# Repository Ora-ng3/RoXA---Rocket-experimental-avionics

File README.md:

RoXA stands for Rocket experimental avionics. It's my first flight computer (that is more than an arduino with a barometer soldered : ), you can see in [this instructables](https://www.instructables.com/Rocket-Flight-Computer/) a more detailed description of the design and build.

In this repo you'll find the PCB design and manufacturing files, as well as the code. For now it can reliably trigger first and second events. I'm working actively on this project to add reliable data logging and telemetry (and many other things...).

Keywords : Flight computer avionics Rocket Reaction wheel Rogallo

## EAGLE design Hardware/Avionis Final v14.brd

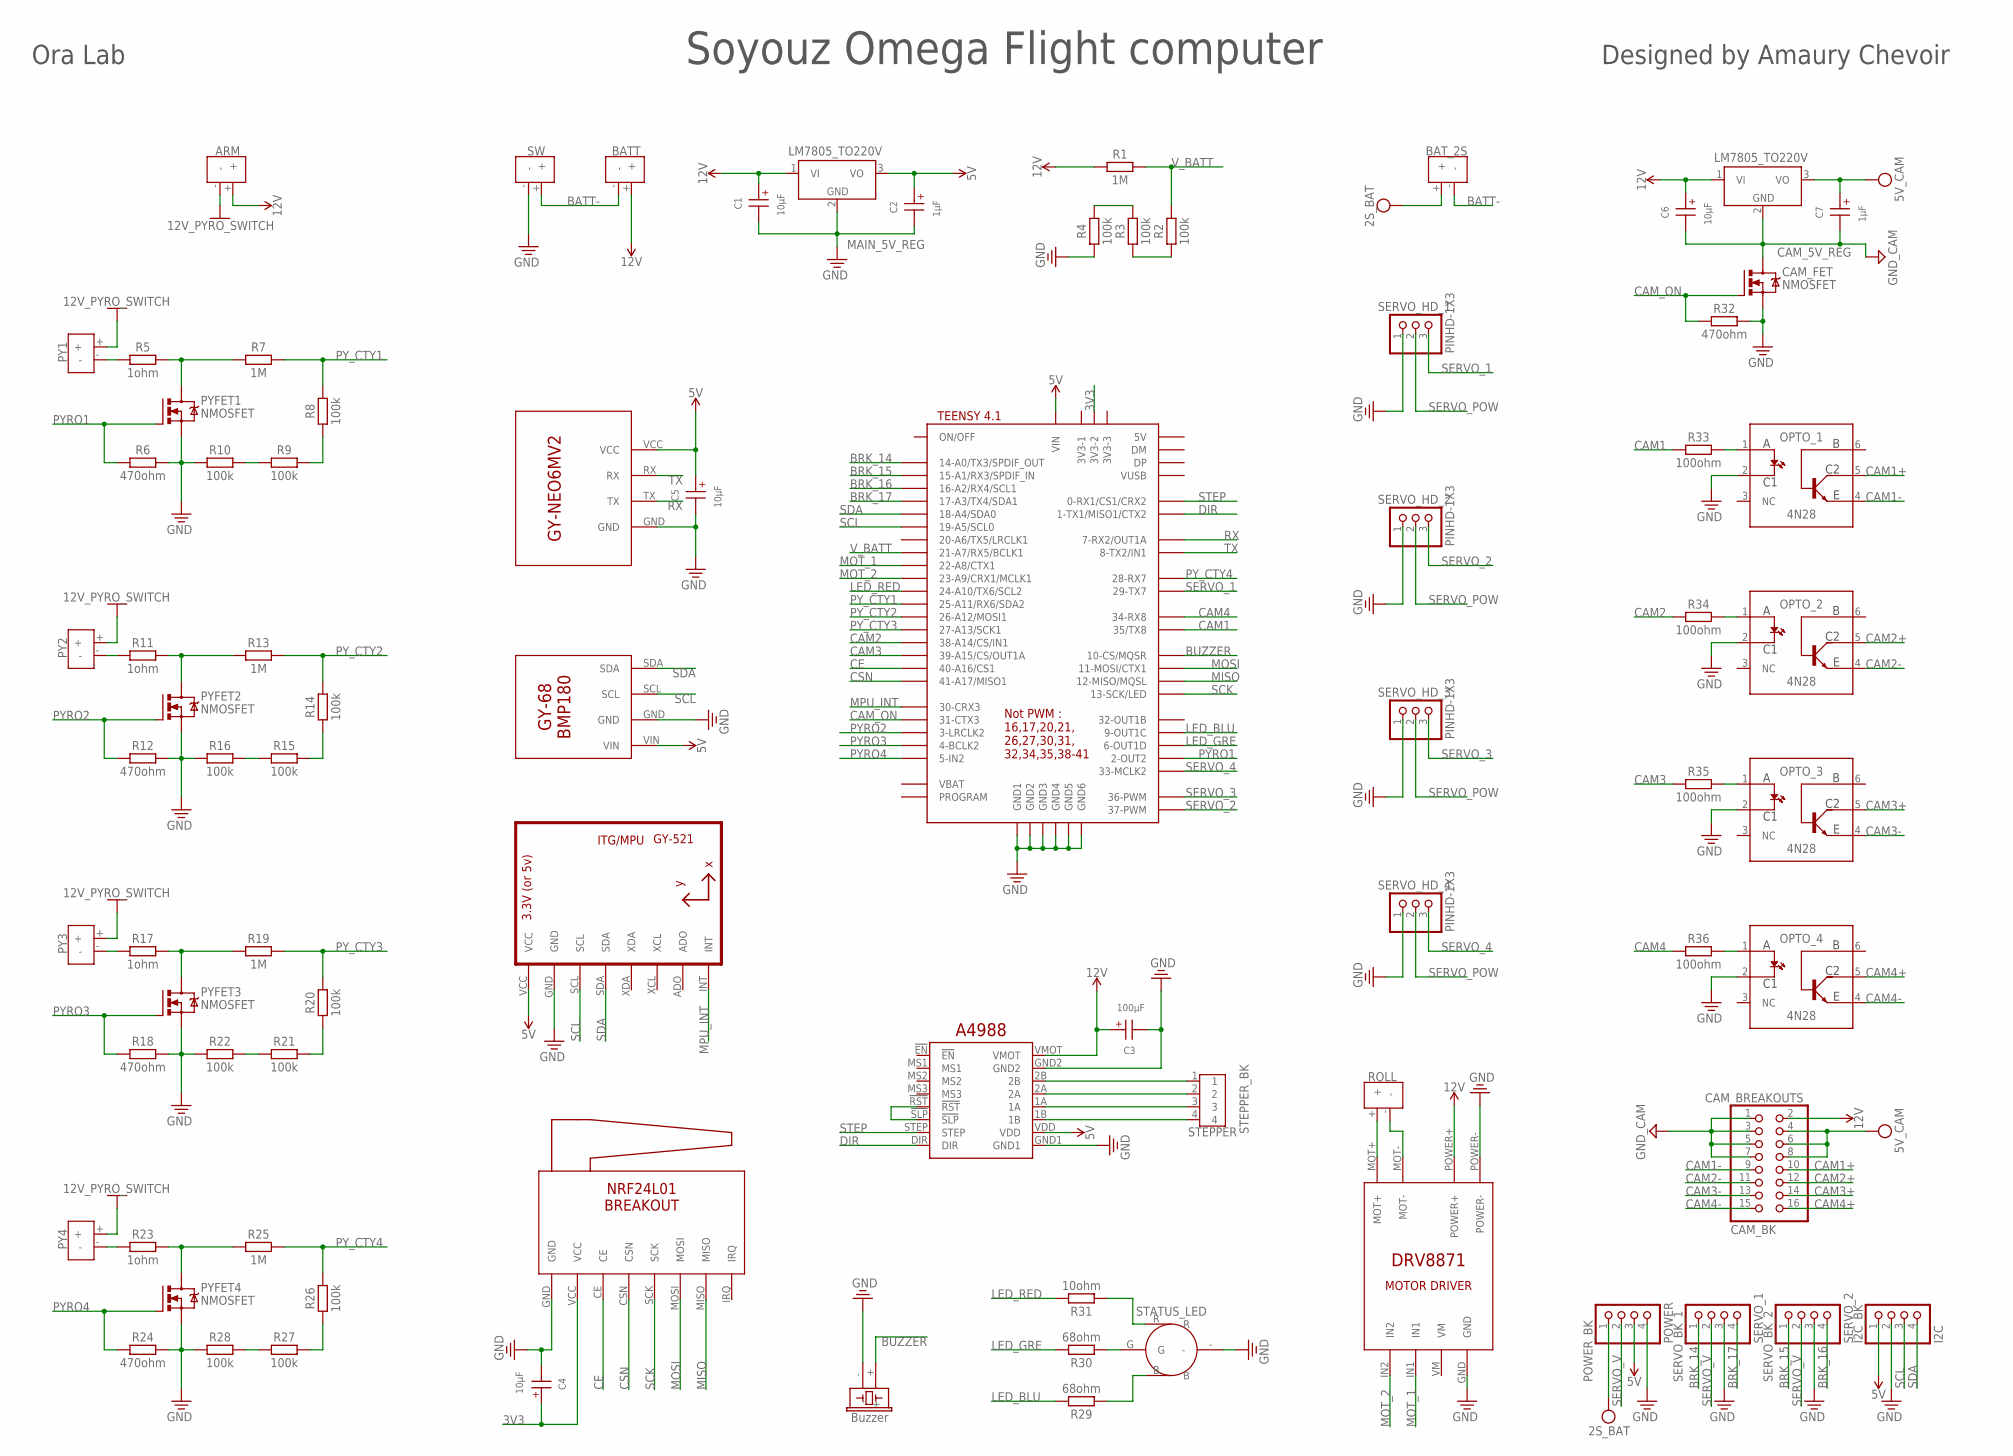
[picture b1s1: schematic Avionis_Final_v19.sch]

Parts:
ARM: TERMBLK_2; TERMBLK_2_LOW
BATT: TERMBLK_2; TERMBLK_2_LOW
BAT_2S: TERMBLK_2; TERMBLK_2_LOW
C1, C4, C5, C6: 10µF; WCAP-AT1H_5X11(DXL)
C2, C7: 1µF; WCAP-AT1H_5X11(DXL)
C3: 100µF; WCAP-AT1H_5X11(DXL)
CAM_5V_REG: LM7805_TO220V; TO220V
CAM_BREAKOUTS: CAM_BK; 2X08
CAM_FET: NMOSFET; TO220BV
I2C_BK: I2C; 1X04
MAIN_5V_REG: LM7805_TO220V; TO220V
OPTO_1, OPTO_2, OPTO_3, OPTO_4: 4N28; DIP762W60P254L712H480Q6B
POWER_BK: POWER; 1X04
PY1, PY2, PY3, PY4: TERMBLK_2; TERMBLK_2_LOW
PYFET1, PYFET2, PYFET3, PYFET4: NMOSFET; TO220BV
R1, R7, R13, R19, R25: 1M; RESAD724W46L381D178B
R2, R3, R4, R8, R9, R10, R14, R15, R16, R20, R21, R22, R26, R27, R28: 100k; RESAD724W46L381D178B
R5, R11, R17, R23: 1ohm; RESAD724W46L381D178B
R6, R12, R18, R24, R32: 470ohm; RESAD724W46L381D178B
R29, R30: 68ohm; RESAD724W46L381D178B
R31: 10ohm; RESAD724W46L381D178B
R33, R34, R35, R36: 100ohm; RESAD724W46L381D178B
ROLL: TERMBLK_2; TERMBLK_2_LOW
SERVO_BK_1: SERVO_1; 1X04
SERVO_BK_2: SERVO_2; 1X04
SERVO_HD_1, SERVO_HD_2, SERVO_HD_3, SERVO_HD_4: PINHD-1X3; 1X03
STATUS_LED: LED_RGB_CAT_THT
STEPPER_BK: STEPPER; B4B-XH-A
SW: TERMBLK_2; TERMBLK_2_LOW
U1: GY-521MPU6050; GY-521
U$1: TEENSY41-E; TENNSY41-E
U$2: NRF24L01_BREAKOUT
U$3: GY-NEO6MV2
U$4: GY-68_BMP180
U$5: DRV8871_MOTORDRIVER
U$6: A4988
U$7: BUZZER_12MM; BUZZER-12MM-KIT

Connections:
1A: STEPPER_BK.3, U$6.1A
1B: STEPPER_BK.4, U$6.1B
2A: STEPPER_BK.2, U$6.2A
2B: STEPPER_BK.1, U$6.2B
2S_BAT: BAT_2S.+, POWER_BK.1
3V3: C4.1 (+), U$1.3V3-2, U$2.VCC
5V: C2.1 (+), C5.1 (+), I2C_BK.1, MAIN_5V_REG.3 (VO), POWER_BK.3, U1.VCC, U$1.VIN, U$3.VCC, U$4.VIN, U$6.VDD
5V_CAM: C7.1 (+), CAM_5V_REG.3 (VO), CAM_BREAKOUTS.4, CAM_BREAKOUTS.6, CAM_BREAKOUTS.8
12V: ARM.+, BATT.+, C1.1 (+), C3.1 (+), C6.1 (+), CAM_5V_REG.1 (VI), CAM_BREAKOUTS.2, MAIN_5V_REG.1 (VI), R1.1, U$5.POWER+, U$6.VMOT
12V_PYRO_SWITCH: ARM.-, PY1.+, PY2.+, PY3.+, PY4.+
!RST: U$6.!RST, U$6.!SLP
BATT-: BATT.-, BAT_2S.-, SW.+
BRK_14: SERVO_BK_1.1, U$1.14-A0/TX3/SPDIF_OUT
BRK_15: SERVO_BK_2.1, U$1.15-A1/RX3/SPDIF_IN
BRK_16: SERVO_BK_2.4, U$1.16-A2/RX4/SCL1
BRK_17: SERVO_BK_1.4, U$1.17-A3/TX4/SDA1
BUZZER: U$1.10-CS\MQSR (10-CS/MQSR), U$7.+
CAM1: R33.1, U$1.35-TX8 (35/TX8)
CAM1+: CAM_BREAKOUTS.10, OPTO_1.5 (C2)
CAM1-: CAM_BREAKOUTS.9, OPTO_1.4 (E)
CAM2: R34.1, U$1.38-A14/CS/IN1
CAM2+: CAM_BREAKOUTS.12, OPTO_2.5 (C2)
CAM2-: CAM_BREAKOUTS.11, OPTO_2.4 (E)
CAM3: R35.1, U$1.39-A15/CS/OUT1A
CAM3+: CAM_BREAKOUTS.14, OPTO_3.5 (C2)
CAM3-: CAM_BREAKOUTS.13, OPTO_3.4 (E)
CAM4: R36.1, U$1.34-RX8
CAM4+: CAM_BREAKOUTS.16, OPTO_4.5 (C2)
CAM4-: CAM_BREAKOUTS.15, OPTO_4.4 (E)
CAM_ON: CAM_FET.G, R32.1, U$1.31-CTX3
CE: U$1.40-A16/CS1, U$2.CE
CSN: U$1.41-A17/MISO1, U$2.CSN
DIR: U$1.1-TX1/MISO1/CTX2, U$6.DIR
GND: C1.2 (-), C2.2 (-), C3.2 (-), C4.2 (-), C5.2 (-), CAM_FET.S, I2C_BK.2, MAIN_5V_REG.2 (GND), OPTO_1.2 (C1), OPTO_2.2 (C1), OPTO_3.2 (C1), OPTO_4.2 (C1), POWER_BK.4, PYFET1.S, PYFET2.S, PYFET3.S, PYFET4.S, R4.1, R6.2, R10.1, R12.2, R16.1, R18.2, R22.1, R24.2, R28.1, R32.2, SERVO_BK_1.3, SERVO_BK_2.3, SERVO_HD_1.1, SERVO_HD_2.1, SERVO_HD_3.1, SERVO_HD_4.1, STATUS_LED.-, SW.-, U1.GND, U$1.GND1, U$1.GND2, U$1.GND3, U$1.GND4, U$1.GND5, U$1.GND6, U$2.GND, U$3.GND, U$4.GND, U$5.GND, U$5.POWER-, U$6.GND1, U$6.GND2, U$7.-
GND_CAM: C6.2 (-), C7.2 (-), CAM_5V_REG.2 (GND), CAM_BREAKOUTS.1, CAM_BREAKOUTS.3, CAM_BREAKOUTS.5, CAM_BREAKOUTS.7, CAM_FET.D
LED_BLU: R29.2, U$1.9-OUT1C
LED_GRE: R30.2, U$1.6-OUT1D
LED_RED: R31.2, U$1.24-A10/TX6/SCL2
MISO: U$1.12-MISO/MQSL, U$2.MISO
MOSI: U$1.11-MOSI/CTX1, U$2.MOSI
MOT_1: U$1.22-A8/CTX1, U$5.IN1
MOT_2: U$1.23-A9/CRX1/MCLK1, U$5.IN2
MPU_INT: U1.INT, U$1.30-CRX3
unnamed: ROLL.+, U$5.MOT+
unnamed: ROLL.-, U$5.MOT-
unnamed: PY2.-, R11.1
unnamed: PYFET2.D, R11.2, R13.1
unnamed: R15.1, R16.2
unnamed: R14.1, R15.2
unnamed: PY3.-, R17.1
unnamed: PY1.-, R5.1
unnamed: R9.1, R10.2
unnamed: PYFET1.D, R5.2, R7.1
unnamed: R2.1, R3.1
unnamed: R3.2, R4.2
unnamed: R8.1, R9.2
unnamed: PYFET3.D, R17.2, R19.1
unnamed: R21.1, R22.2
unnamed: R20.1, R21.2
unnamed: PY4.-, R23.1
unnamed: PYFET4.D, R23.2, R25.1
unnamed: R27.1, R28.2
unnamed: R26.1, R27.2
unnamed: R30.1, STATUS_LED.G
unnamed: R31.1, STATUS_LED.R
unnamed: OPTO_1.1 (A), R33.2
unnamed: R29.1, STATUS_LED.B
unnamed: OPTO_2.1 (A), R34.2
unnamed: OPTO_3.1 (A), R35.2
unnamed: OPTO_4.1 (A), R36.2
PYRO1: PYFET1.G, R6.1, U$1.2-OUT2
PYRO2: PYFET2.G, R12.1, U$1.3-LRCLK2
PYRO3: PYFET3.G, R18.1, U$1.4-BCLK2
PYRO4: PYFET4.G, R24.1, U$1.5-IN2
PY_CTY1: R7.2, R8.2, U$1.25-A11/RX6/SDA2
PY_CTY2: R13.2, R14.2, U$1.26-A12/MOSI1
PY_CTY3: R19.2, R20.2, U$1.27-A13/SCK1
PY_CTY4: R25.2, R26.2, U$1.28-RX7
RX: U$1.7-RX2/OUT1A, U$3.TX
SCK: U$1.13-SCK/LED, U$2.SCK
SCL: I2C_BK.3, U1.SCL, U$1.19-A5/SCL0, U$4.SCL
SDA: I2C_BK.4, U1.SDA, U$1.18-A4/SDA0, U$4.SDA
SERVO_1: SERVO_HD_1.3, U$1.29-TX7
SERVO_2: SERVO_HD_2.3, U$1.37-PWM
SERVO_3: SERVO_HD_3.3, U$1.36-PWM
SERVO_4: SERVO_HD_4.3, U$1.33-MCLK2
SERVO_POW: SERVO_HD_1.2, SERVO_HD_2.2, SERVO_HD_3.2, SERVO_HD_4.2
SERVO_V: POWER_BK.2, SERVO_BK_1.2, SERVO_BK_2.2
STEP: U$1.0-RX1/CS1/CRX2, U$6.STEP
TX: U$1.8-TX2/IN1, U$3.RX
V_BATT: R1.2, R2.2, U$1.21-A7/RX5/BCLK1

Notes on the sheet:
Soyouz Omega Flight computer
Ora Lab
Designed by Amaury Chevoir

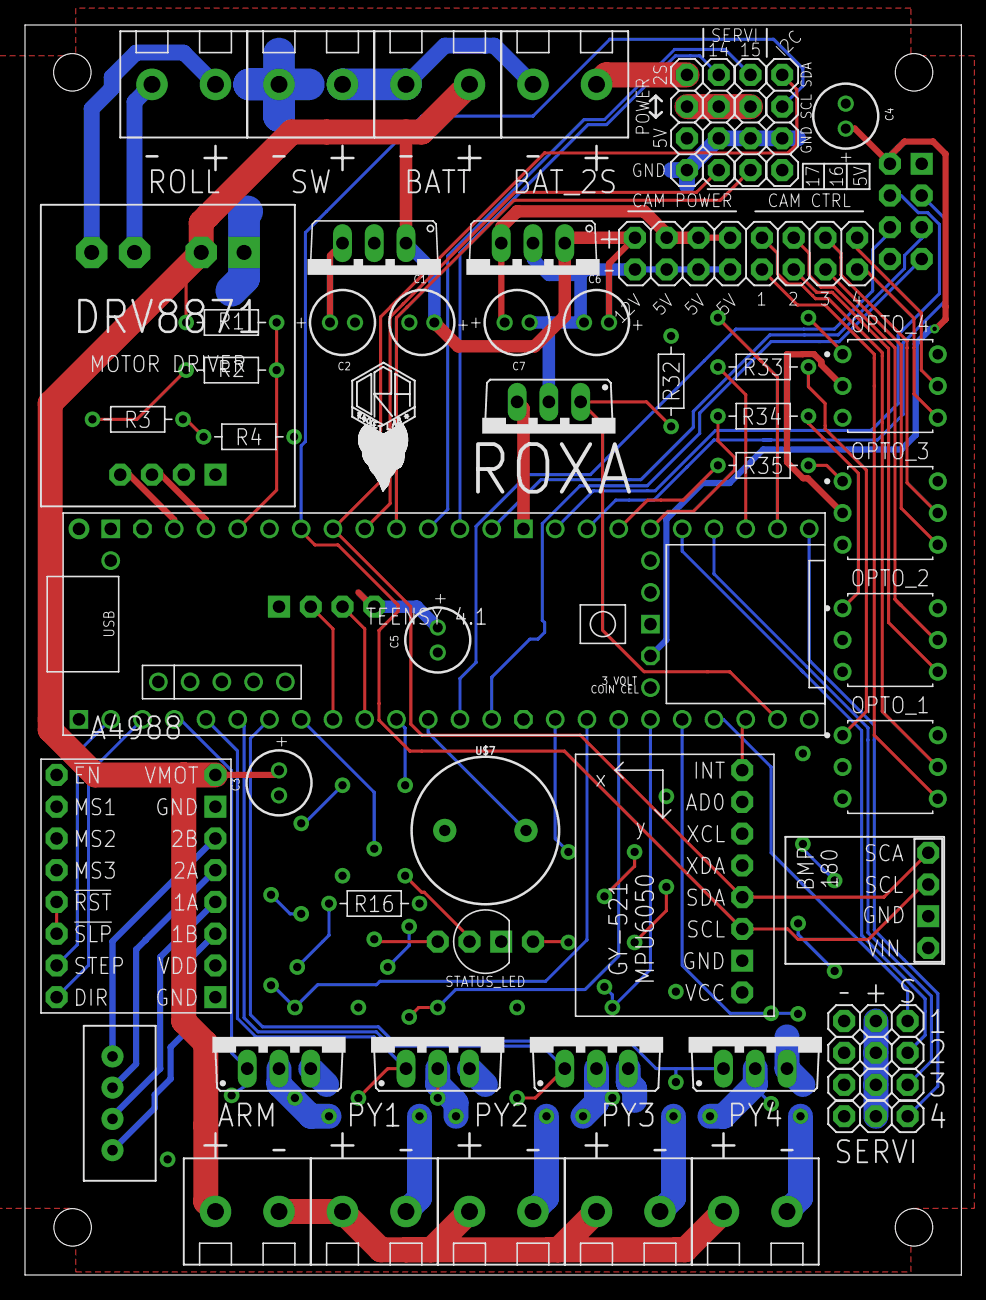
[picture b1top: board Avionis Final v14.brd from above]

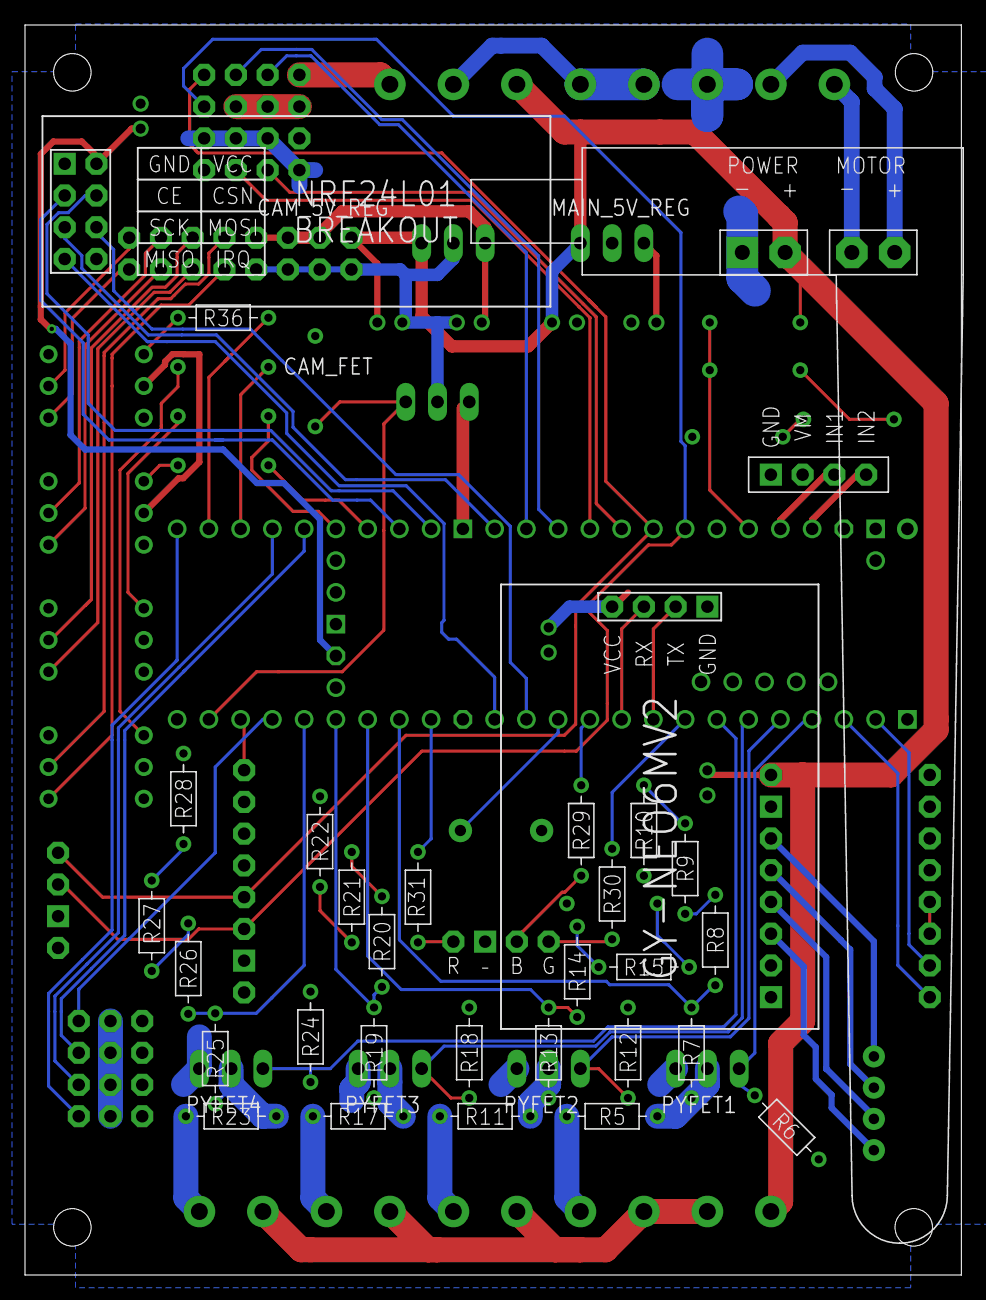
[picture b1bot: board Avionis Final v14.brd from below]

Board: 2 copper layers, 74.9 x 100.0 mm, 82 parts (29 on the bottom side), 91 nets.

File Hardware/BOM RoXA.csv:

Qty,Device,Value,Parts,Unit Price,Price
1,Microcontroller,Teensy 4.1,U$1,"40,00 €","40,00 €"
1,Barometer,GY-68 BMP180,U$4,"2,00 €","2,00 €"
1,IMU,GY-521 MPU6050,U1,"2,50 €","2,50 €"
1,GPS,GY-NEO6MV2,U$3,"10,00 €","10,00 €"
1,Radio Module,NRF24L01+PA+LNA,U$2,"4,00 €","4,00 €"
1,Motor Driver,DRV8871,U$5,"8,00 €","8,00 €"
1,Stepper Driver,A4988,U$6,"2,00 €","2,00 €"
1,RGB Led,5mm Com. Cat.,STATUS_LED,"0,10 €","0,10 €"
1,Buzzer,3.3V 12mm,U$7,"1,00 €","1,00 €"
2,5V Regulator,L7805CV TO220V,"CAM_5V_REG, MAIN_5V_REG","0,80 €","1,60 €"
5,N-Mosfet,IRFZ44N TO220V,"CAM_FET, PYFET1, PYFET2, PYFET3, PYFET4","0,80 €","4,00 €"
15,Resistor,100k,"R2, R3, R4, R8, R9, R10, R14, R15, R16, R20, R21, R22, R26, R27, R28","0,05 €","0,75 €"
4,Resistor,1ohm,"R5, R11, R17, R23","0,05 €","0,20 €"
1,Resistor,10ohm,R31,"0,05 €","0,05 €"
2,Resistor,68ohm,"R29, R30","0,05 €","0,10 €"
4,Resistor,100ohm,"R33, R34, R35, R36","0,05 €","0,20 €"
5,Resistor,470ohm,"R6, R12, R18, R24, R32","0,05 €","0,25 €"
5,Resistor,1M,"R1, R7, R13, R19, R25","0,05 €","0,25 €"
2,Capacitor,1µF,"C2, C7","0,15 €","0,30 €"
4,Capacitor,10µF,"C1, C4, C5, C6","0,15 €","0,60 €"
1,Capacitor,100µF,C3,"0,15 €","0,15 €"
4,Optocoupler,4N28,"OPTO_1, OPTO_2, OPTO_3, OPTO_4","0,15 €","0,60 €"
8,Headers,2 pins,CAM_BREAKOUTS,"0,01 €","0,08 €"
4,Headers,3 pins,"SERVO_HD_1, SERVO_HD_2, SERVO_HD_3, SERVO_HD_4","0,01 €","0,04 €"
4,Headers,4 pins,POWER_BK,"0,01 €","0,04 €"
1,Stepper connector,4 pins JST XH,STEPPER_BK,"0,10 €","0,10 €"
9,Screw terminals,2 pins 5mm,"ARM, BATT, BAT_2S, PY1, PY2, PY3, PY4, ROLL, SW","0,10 €","0,90 €"
1,PCB Board,,,"2,00 €","2,00 €"
,,,,,
,,,,Total :,"81,81 €"

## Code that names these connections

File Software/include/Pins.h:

// Pin definitions for ROXA
#ifndef PINS_H
#define PINS_H

constexpr int STEP = 0;
constexpr int DIR = 1;
constexpr int PYRO1 = 2;
constexpr int PYRO2 = 3;
constexpr int PYRO3 = 4;
constexpr int PYRO4 = 5;
constexpr int LED_B = 6;
constexpr int RX = 7;
constexpr int TX = 8;
constexpr int LED_G = 9;
constexpr int BUZZER = 10;
// MOSI = 11
// MISO = 12
//constexpr int SCK = 13; (already defined in core_pins.h from teensy)
constexpr int BRK_14 = 14; // Top
constexpr int BRK_15 = 15; // Bottom
constexpr int BRK_16 = 16;
constexpr int BRK_17 = 17;
// SDA = 18
// SCL = 19
// 20 : unused (A6, TX5, LRCLK1)
constexpr int BATT = 21;
constexpr int MOT_1 = 22;
constexpr int MOT_2 = 23;
constexpr int LED_R = 24;
constexpr int PYRO_CTY1 = 25;
constexpr int PYRO_CTY2 = 26;
constexpr int PYRO_CTY3 = 27;
constexpr int PYRO_CTY4 = 28;
constexpr int SERVO_1 = 29;
// 30 : unused (CRX3)
// 31 : unused (CTX3)
// 32 : unused (OUT1B)
constexpr int SERVO_4 = 33;
constexpr int CAM_4 = 34;
constexpr int CAM_1 = 35;
constexpr int SERVO_3 = 36;
constexpr int SERVO_2 = 37;
constexpr int CAM_2 = 38;
constexpr int CAM_3 = 39;
constexpr int NRF_CE = 40;
constexpr int NRF_CSN = 41;

#endif

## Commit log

2024-10-15 Added link to the instructables

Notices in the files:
parts and their libraries:
Wurth_Capacitors_WCAP-AT1H: Copyright: Würth Elektronik
SparkFun-PowerSymbols: Licensing: Creative Commons ShareAlike 4.0 International - https://creativecommons.org/licenses/by-sa/4.0
